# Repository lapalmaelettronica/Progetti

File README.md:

# Progetti
Una lista dei progetti che ho pubblicato su instagram, potete trovarci pcb, codici, schemi elettrici e stampe 3d!

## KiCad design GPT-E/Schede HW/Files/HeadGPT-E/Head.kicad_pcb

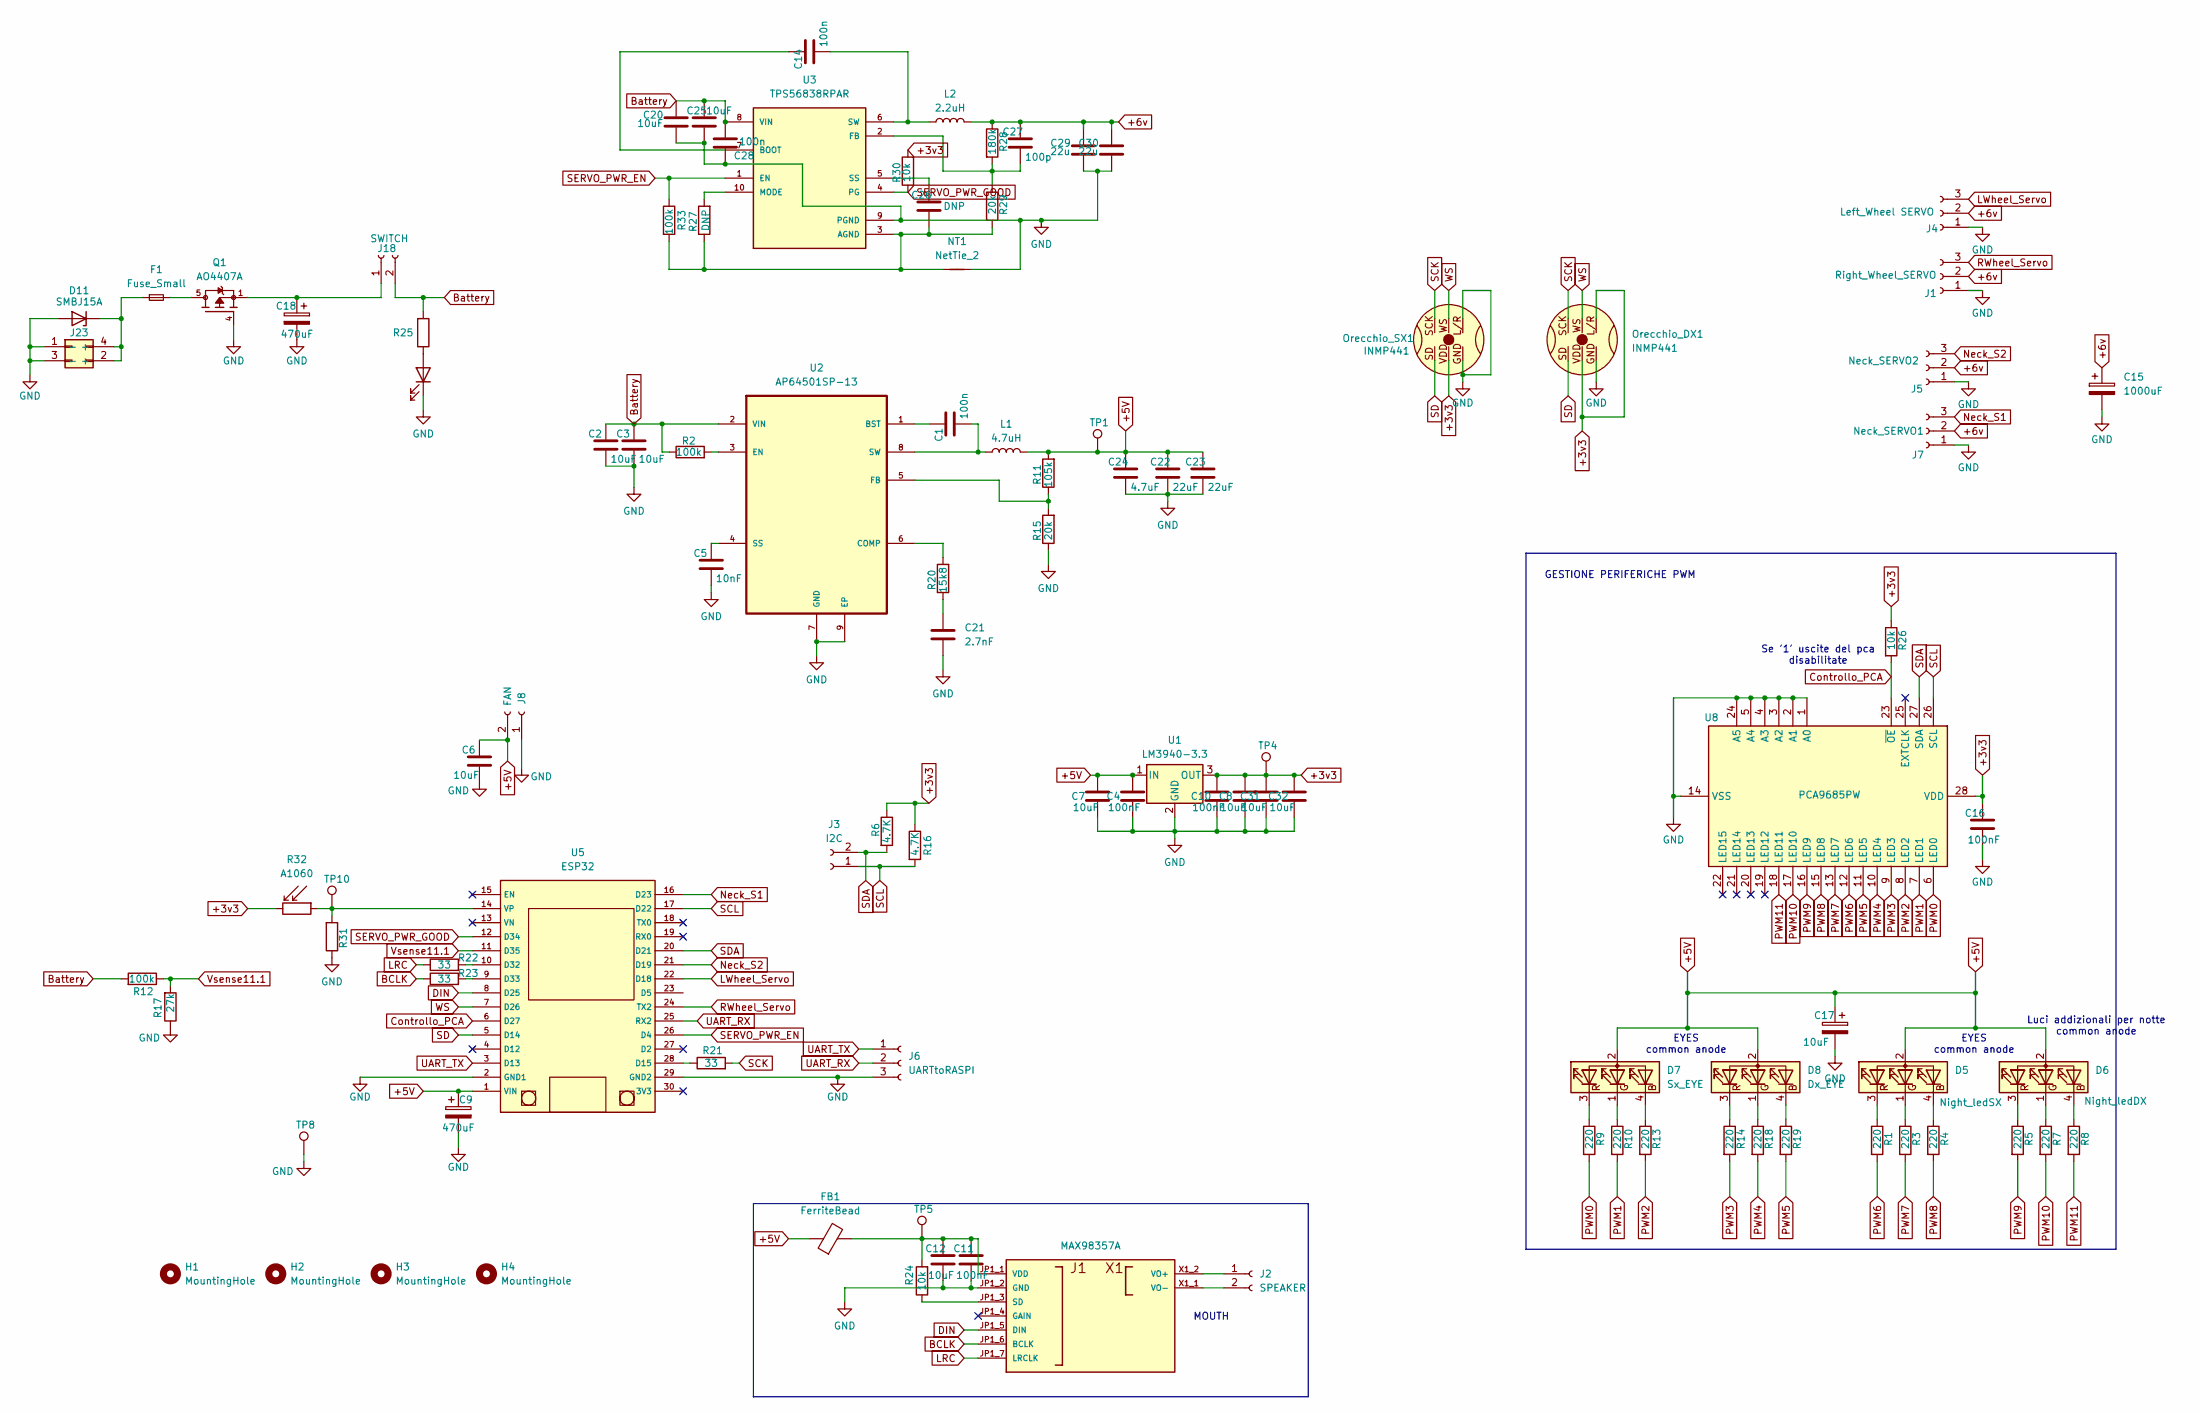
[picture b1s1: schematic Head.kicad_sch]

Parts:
C1, C14, C28: 100n; C_0805_2012Metric_Pad1.18x1.45mm_HandSolder
C2, C3, C6, C7, C8, C12, C20, C25, C31, C32: 10uF; C_0805_2012Metric_Pad1.18x1.45mm_HandSolder
C4, C10, C11, C16: 100nF; C_0805_2012Metric_Pad1.18x1.45mm_HandSolder
C5: 10nF; C_0805_2012Metric_Pad1.18x1.45mm_HandSolder
C9, C18: 470uF; CP_Radial_D5.0mm_P2.00mm
C15: 1000uF; CP_Radial_D12.5mm_P5.00mm
C17: 10uF; CP_Radial_D5.0mm_P2.00mm
C21: 2.7nF; C_Disc_D5.0mm_W2.5mm_P2.50mm
C22, C23: 22uF; C_0805_2012Metric_Pad1.18x1.45mm_HandSolder
C24: 4.7uF; C_0805_2012Metric_Pad1.18x1.45mm_HandSolder
C26: DNP; C_0805_2012Metric_Pad1.18x1.45mm_HandSolder
C27: 100p; C_0805_2012Metric_Pad1.18x1.45mm_HandSolder
C29, C30: 22u; C_0805_2012Metric_Pad1.18x1.45mm_HandSolder
D5: Night_ledSX; NS-Tech_Grove_1x04_P2mm_Vertical
D6: Night_ledDX; NS-Tech_Grove_1x04_P2mm_Vertical
D7: Sx_EYE; NS-Tech_Grove_1x04_P2mm_Vertical
D8: Dx_EYE; NS-Tech_Grove_1x04_P2mm_Vertical
D11: SMBJ15A; D_SMB_Handsoldering
D13: LED; LED_D4.0mm
F1: Fuse_Small; Fuseholder_Littelfuse_Nano2_154x
FB1: FerriteBead; L_0805_2012Metric_Pad1.05x1.20mm_HandSolder
H1, H2, H3, H4: MountingHole; MountingHole_3.2mm_M3_DIN965
J1: Right_Wheel_SERVO; Molex_KK-254_AE-6410-03A_1x03_P2.54mm_Vertical
J2: SPEAKER; Molex_KK-254_AE-6410-02A_1x02_P2.54mm_Vertical
J3: I2C; Molex_KK-254_AE-6410-02A_1x02_P2.54mm_Vertical
J4: Left_Wheel SERVO; Molex_KK-254_AE-6410-03A_1x03_P2.54mm_Vertical
J5: Neck_SERVO2; Molex_KK-254_AE-6410-03A_1x03_P2.54mm_Vertical
J6: UARTtoRASPI; Molex_KK-254_AE-6410-03A_1x03_P2.54mm_Vertical
J7: Neck_SERVO1; Molex_KK-254_AE-6410-03A_1x03_P2.54mm_Vertical
J8: FAN; Molex_KK-254_AE-6410-02A_1x02_P2.54mm_Vertical
J18: SWITCH; PinHeader_1x02_P2.54mm_Vertical
J23: Molex_Micro-Fit_3.0_43045-0400_2x02_P3.00mm_Horizontal
L1: 4.7uH; L_Changjiang_FXL0630
L2: 2.2uH; L_Changjiang_FXL0630
NT1: NetTie_2; NetTie-2_SMD_Pad0.5mm
Orecchio_DX1: INMP441
Orecchio_SX1: INMP441
Q1: AO4407A; SOIC127P600X175-8N; PARTREV I
R1, R3, R4, R5, R7, R8, R9, R10, R13, R14, R18, R19: 220; R_1206_3216Metric_Pad1.30x1.75mm_HandSolder
R2, R12, R33: 100k; R_1206_3216Metric_Pad1.30x1.75mm_HandSolder
R6, R16: 4.7K; R_1206_3216Metric_Pad1.30x1.75mm_HandSolder
R11: 105k; R_1206_3216Metric_Pad1.30x1.75mm_HandSolder
R15, R29: 20k; R_1206_3216Metric_Pad1.30x1.75mm_HandSolder
R17: 27k; R_1206_3216Metric_Pad1.30x1.75mm_HandSolder
R20: 15k8; R_1206_3216Metric_Pad1.30x1.75mm_HandSolder
R21, R22, R23: 33; R_1206_3216Metric_Pad1.30x1.75mm_HandSolder
R24, R26, R30, R31: 10k; R_1206_3216Metric_Pad1.30x1.75mm_HandSolder
R25: 470; R_1206_3216Metric_Pad1.30x1.75mm_HandSolder
R27: DNP; R_1206_3216Metric_Pad1.30x1.75mm_HandSolder
R28: 180k; R_1206_3216Metric_Pad1.30x1.75mm_HandSolder
R32: A1060; R_LDR_D6.4mm_P3.4mm_Vertical
TP1, TP4, TP5, TP8, TP10: TestPoint; TestPoint_Pad_D1.5mm
U1: LM3940-3.3; SOT-223-3_TabPin2
U2: AP64501SP-13
U3: TPS56838RPAR; CONV_TPS56838RPAR; PARTREV A
U5: ESP32
U7: MAX98357A; PARTREV A
U8: PCA9685PW; TSSOP-28_4.4x9.7mm_P0.65mm

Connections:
+3v3: C8.1, C10.1, C16.1, C31.1, C32.1, Orecchio_DX1.L/R, Orecchio_DX1.VDD, Orecchio_SX1.VDD, R6.1, R16.1, R26.1, R30.2, R32.2, TP4.1, U1.3 (OUT), U8.28 (VDD)
+5V: C4.1, C6.1, C7.1, C9.1, C17.1, C22.1, C23.1, C24.1, D5.2 (A), D6.2 (A), D7.2 (A), D8.2 (A), FB1.1, J8.2, L1.2, R11.2, TP1.1, U1.1 (IN), U5.1 (VIN)
+6v: C15.1, C27.1, C29.1, C30.1, J1.2, J4.2, J5.2, J7.2, L2.2, R28.1
BCLK: R23.1, U7.JP1_6 (BCLK)
Battery: C2.1, C3.1, C20.1, C25.1, C28.2, J18.2, R2.1, R12.2, R25.2, U2.2 (VIN), U3.8 (VIN)
Controllo_PCA: R26.2, U5.6 (D27), U8.23 (~OE)
DIN: U5.8 (D25), U7.JP1_5 (DIN)
GND: C2.2, C3.2, C4.2, C5.2, C6.2, C7.2, C8.2, C9.2, C10.2, C11.2, C12.2, C15.2, C16.2, C17.2, C18.2, C20.2, C21.2, C22.2, C23.2, C24.2, C25.2, C28.1, C29.2, C30.2, C31.2, C32.2, D11.2 (A), D13.1 (K), J1.1, J4.1, J5.1, J6.3, J7.1, J8.1, J23.1 (-), J23.3 (-), NT1.1, Orecchio_DX1.GND, Orecchio_SX1.GND, Orecchio_SX1.L/R, Q1.4, R15.1, R17.1, R31.1, TP8.1, U1.2 (GND), U2.7 (GND), U2.9 (EP), U3.9 (PGND), U5.2 (GND1), U5.29 (GND2), U7.JP1_2 (GND), U8.1 (A0), U8.2 (A1), U8.3 (A2), U8.4 (A3), U8.5 (A4), U8.14 (VSS), U8.24 (A5)
LRC: R22.1, U7.JP1_7 (LRCLK)
LWheel_Servo: J4.3, U5.22 (D18)
Neck_S1: J7.3, U5.16 (D23)
Neck_S2: J5.3, U5.21 (D19)
unnamed: C21.1, R20.1
unnamed: D5.4 (BK), R4.1
unnamed: D5.1 (GK), R3.1
unnamed: D5.3 (RK), R1.1
unnamed: D6.4 (BK), R8.1
unnamed: D6.1 (GK), R7.1
unnamed: D6.3 (RK), R5.1
unnamed: D7.4 (BK), R13.1
unnamed: D7.1 (GK), R10.1
unnamed: D7.3 (RK), R9.1
unnamed: D8.4 (BK), R19.1
unnamed: D8.1 (GK), R18.1
unnamed: D8.3 (RK), R14.1
unnamed: D11.1 (K), F1.1, J23.2 (+), J23.4 (+)
unnamed: D13.2 (A), R25.1
unnamed: F1.2, Q1.5, Q1.6, Q1.7, Q1.8
unnamed: J2.1, U7.X1_2 (VO+)
unnamed: J2.2, U7.X1_1 (VO-)
unnamed: C18.1, J18.1, Q1.1, Q1.2, Q1.3
unnamed: C1.1, U2.1 (BST)
unnamed: R20.2, U2.6 (COMP)
unnamed: R2.2, U2.3 (EN)
unnamed: R11.1, R15.2, U2.5 (FB)
unnamed: C5.1, U2.4 (SS)
unnamed: C1.2, L1.1, U2.8 (SW)
unnamed: C26.2, NT1.2, R27.1, R29.2, R33.2, U3.3 (AGND)
unnamed: C14.1, U3.7 (BOOT)
unnamed: C27.2, R28.2, R29.1, U3.2 (FB)
unnamed: R27.2, U3.10 (MODE)
unnamed: C26.1, U3.5 (SS)
unnamed: C14.2, L2.1, U3.6 (SW)
unnamed: R21.1, U5.28 (D15)
unnamed: R22.2, U5.10 (D32)
unnamed: R23.2, U5.9 (D33)
unnamed: R31.2, R32.1, TP10.1, U5.14 (VP)
unnamed: R24.1, U7.JP1_3 (SD)
unnamed: C11.1, C12.1, FB1.2, R24.2, TP5.1, U7.JP1_1 (VDD)
PWM0: R9.2, U8.6 (LED0)
PWM1: R10.2, U8.7 (LED1)
PWM2: R13.2, U8.8 (LED2)
PWM3: R14.2, U8.9 (LED3)
PWM4: R18.2, U8.10 (LED4)
PWM5: R19.2, U8.11 (LED5)
PWM6: R1.2, U8.12 (LED6)
PWM7: R3.2, U8.13 (LED7)
PWM8: R4.2, U8.15 (LED8)
PWM9: R5.2, U8.16 (LED9)
PWM10: R7.2, U8.17 (LED10)
PWM11: R8.2, U8.18 (LED11)
RWheel_Servo: J1.3, U5.24 (TX2)
SCK: Orecchio_DX1.SCK, Orecchio_SX1.SCK, R21.2
SCL: J3.1, R16.2, U5.17 (D22), U8.26 (SCL)
SD: Orecchio_DX1.SD, Orecchio_SX1.SD, U5.5 (D14)
SDA: J3.2, R6.2, U5.20 (D21), U8.27 (SDA)
SERVO_PWR_EN: R33.1, U3.1 (EN), U5.26 (D4)
SERVO_PWR_GOOD: R30.1, U3.4 (PG), U5.12 (D34)
UART_RX: J6.2, U5.25 (RX2)
UART_TX: J6.1, U5.3 (D13)
Vsense11.1: R12.1, R17.2, U5.11 (D35)
WS: Orecchio_DX1.WS, Orecchio_SX1.WS, U5.7 (D26)

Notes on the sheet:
MOUTH
GESTIONE PERIFERICHE PWM
Se '1' uscite del pca disabilitate
EYES common anode
Luci addizionali per notte common anode

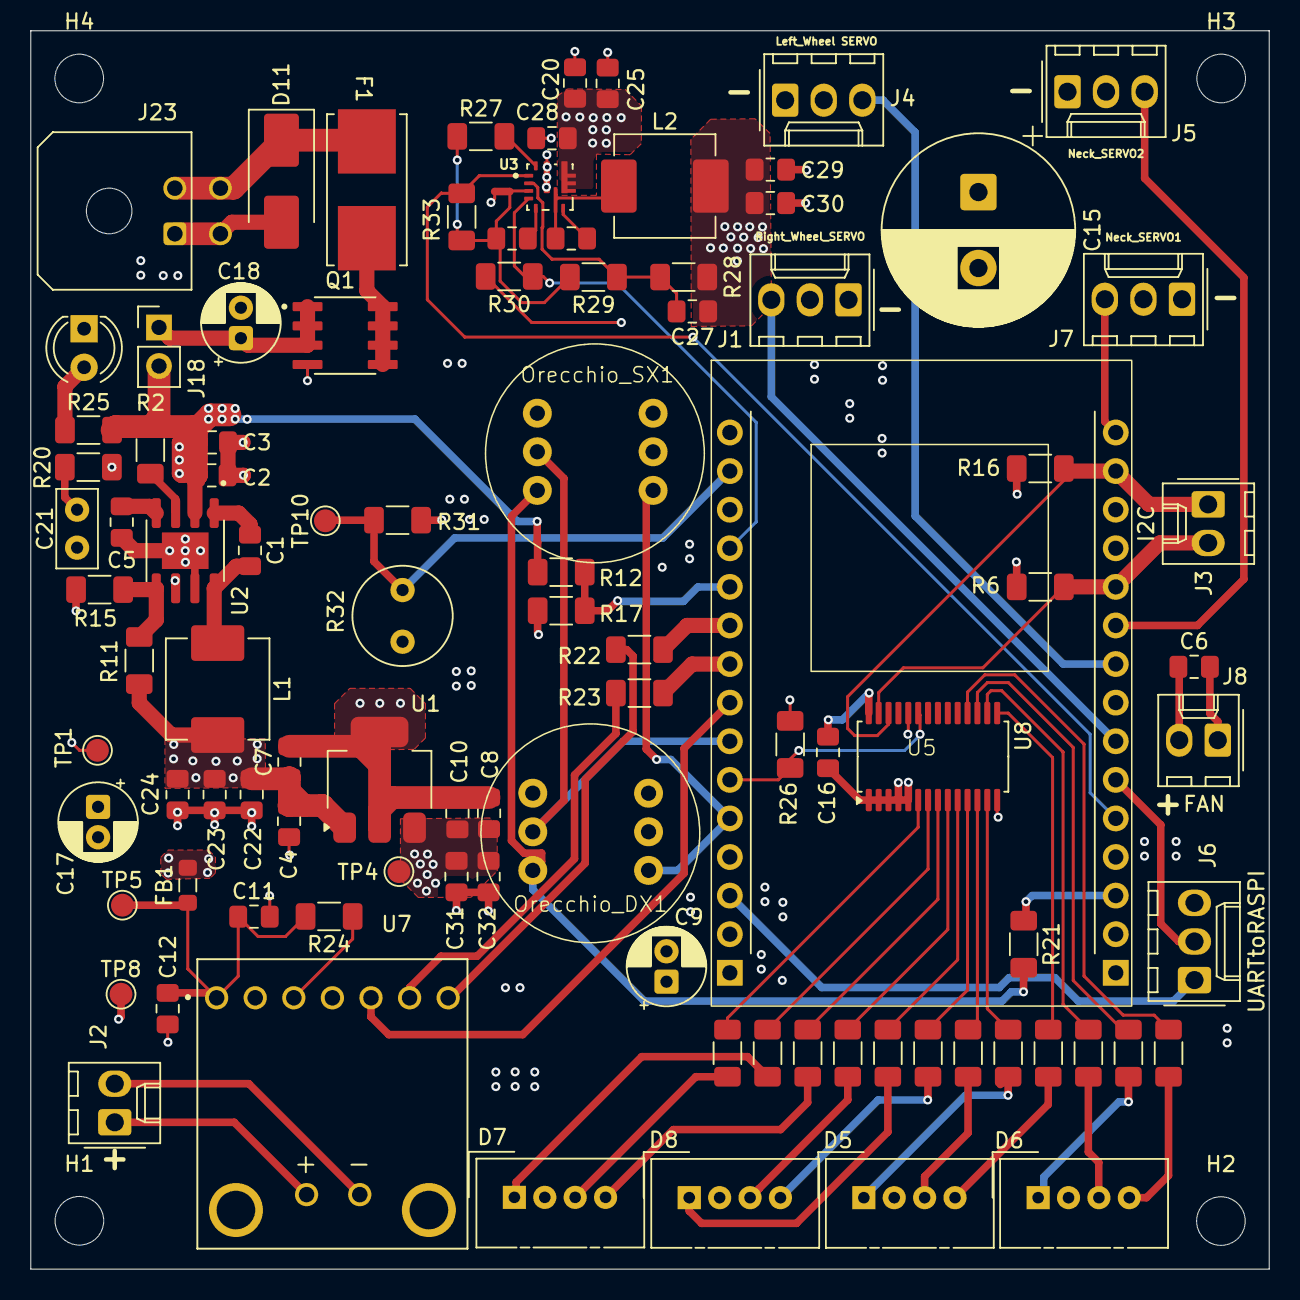
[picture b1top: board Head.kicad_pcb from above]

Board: 4 copper layers, 81.5 x 81.5 mm, 102 parts (0 on the bottom side), 72 nets.

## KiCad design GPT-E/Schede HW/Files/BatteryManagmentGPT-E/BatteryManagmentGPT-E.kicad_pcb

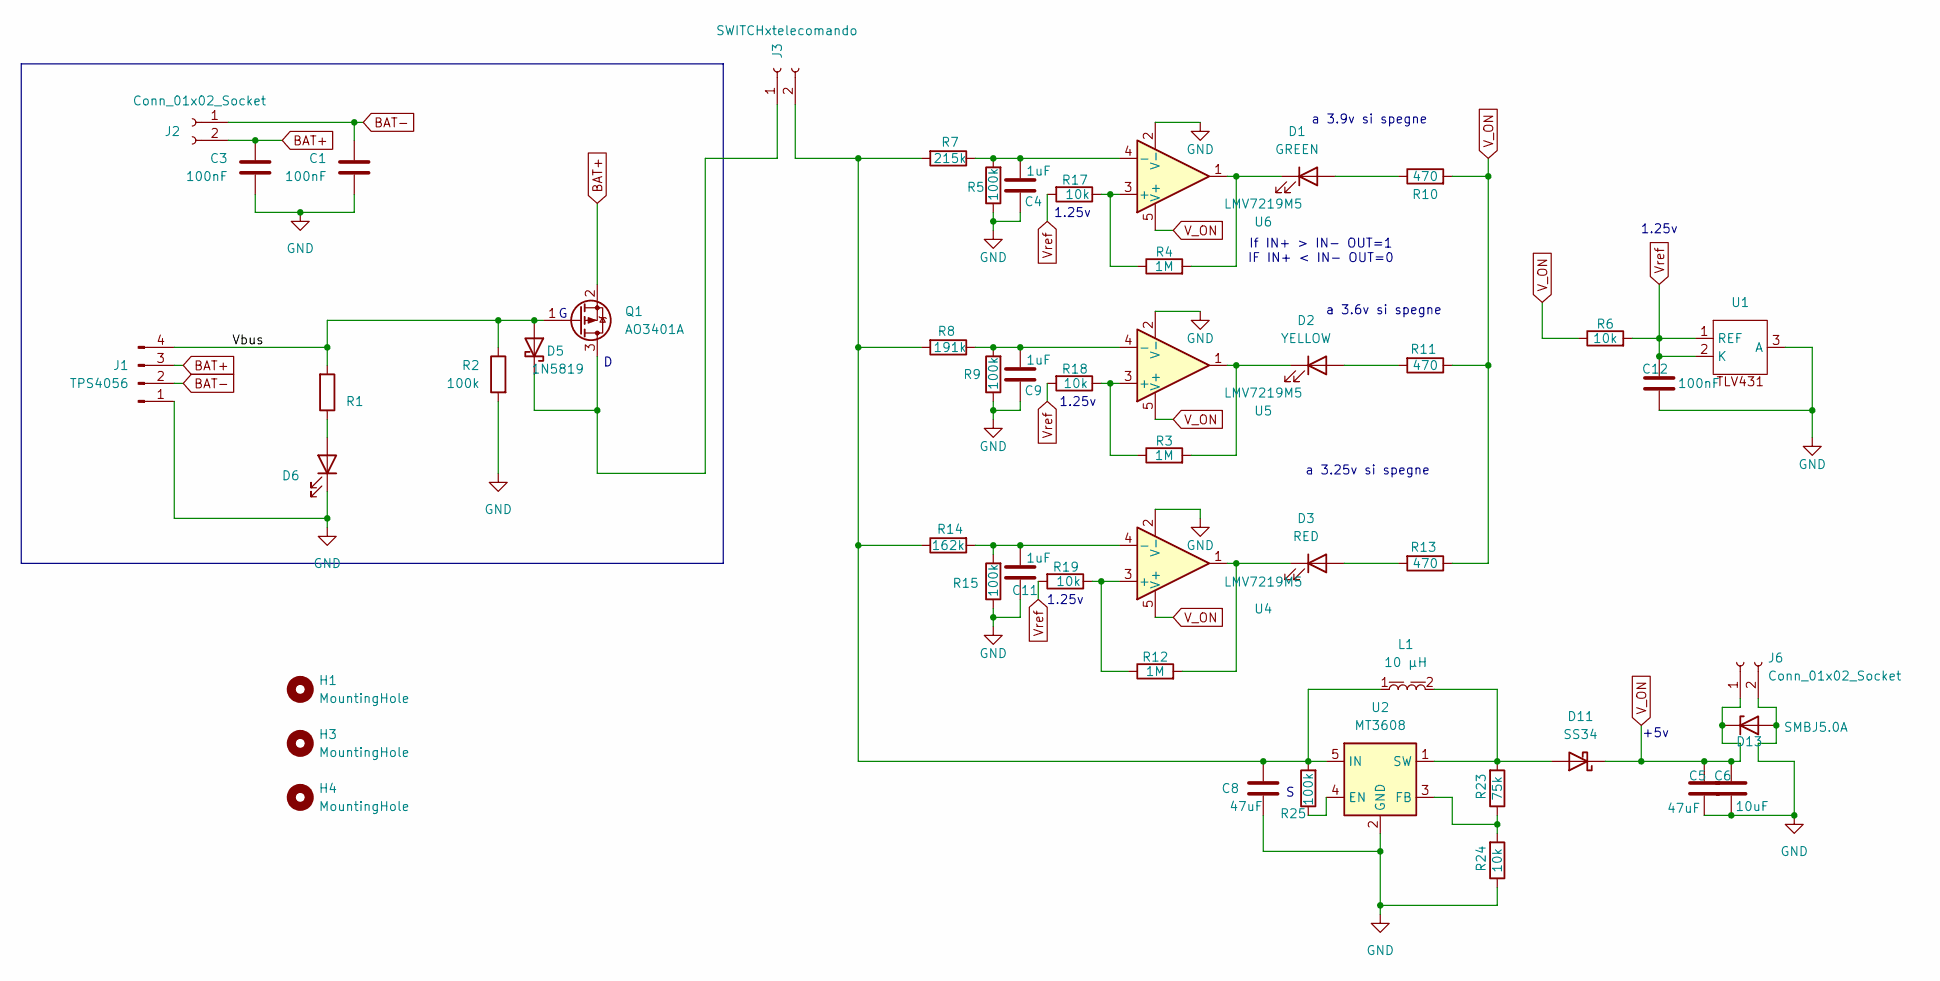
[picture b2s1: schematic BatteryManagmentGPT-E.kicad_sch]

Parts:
C1, C3, C12: 100nF; C_0805_2012Metric
C4, C9, C11: 1uF; C_0805_2012Metric
C5, C8: 47uF; C_0805_2012Metric
C6: 10uF; C_0805_2012Metric
D1: GREEN; LED_D4.0mm
D2: YELLOW; LED_D4.0mm
D3: RED; LED_D4.0mm
D5: 1N5819; D_DO-41_SOD81_P7.62mm_Horizontal
D6: LED; LED_D4.0mm
D11: SS34; D_SMB_Handsoldering
D13: SMBJ5.0A; D_SMB_Handsoldering
H1, H3, H4: MountingHole; MountingHole_2.2mm_M2
J1: TPS4056; Molex_KK-254_AE-6410-04A_1x04_P2.54mm_Vertical
J2, J6: Conn_01x02_Socket; TE_440054-2_1x02_P2.00mm_Vertical
J3: SWITCHxtelecomando; PinHeader_1x02_P2.54mm_Vertical
L1: Induttore 4020_7843845030100; L_Coilcraft_XxL4020; Part Number 78438440200016
Q1: AO3401A; SOT-23
R1, R10, R11, R13: 470; R_1206_3216Metric
R2, R5, R9, R15, R25: 100k; R_1206_3216Metric
R3, R4, R12: 1M; R_1206_3216Metric
R6, R17, R18, R19, R24: 10k; R_1206_3216Metric
R7: 215k; R_1206_3216Metric
R8: 191k; R_1206_3216Metric
R14: 162k; R_1206_3216Metric
R23: 75k; R_1206_3216Metric
U1: SOT-23-3
U2: MT3608; SOT-23-6_Handsoldering
U4, U5, U6: LMV7219M5; SOT-23-5_HandSoldering

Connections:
/Vbus: D5.2 (A), J1.4, Q1.1 (G), R1.2, R2.1
BAT+: C3.1, J1.3, J2.2, Q1.2 (S)
BAT-: C1.1, J1.2, J2.1
GND: C1.2, C3.2, C4.2, C5.2, C6.2, C8.2, C9.2, C11.2, C12.2, D6.1 (K), D13.2 (A), J1.1, J6.2, R2.2, R5.1, R9.1, R15.1, R24.1, U1.3 (A), U2.2 (GND), U4.2 (V-), U5.2 (V-), U6.2 (V-)
unnamed: D1.2 (A), R10.1
unnamed: D1.1 (K), R4.2, U6.1
unnamed: D2.2 (A), R11.2
unnamed: D2.1 (K), R3.2, U5.1
unnamed: D3.2 (A), R13.2
unnamed: D3.1 (K), R12.2, U4.1
unnamed: D5.1 (K), J3.1, Q1.3 (D)
unnamed: D6.2 (A), R1.1
unnamed: D11.2 (A), L1.2, R23.2, U2.1 (SW)
unnamed: C8.1, J3.2, L1.1, R7.2, R8.2, R14.1, R25.2, U2.5 (IN)
unnamed: R25.1, U2.4 (EN)
unnamed: R23.1, R24.2, U2.3 (FB)
unnamed: R12.1, R19.1, U4.3 (+)
unnamed: C11.1, R14.2, R15.2, U4.4 (-)
unnamed: R3.1, R18.1, U5.3 (+)
unnamed: C9.1, R8.1, R9.2, U5.4 (-)
unnamed: R4.1, R17.1, U6.3 (+)
unnamed: C4.1, R5.2, R7.1, U6.4 (-)
V_ON: C5.1, C6.1, D11.1 (K), D13.1 (K), J6.1, R6.1, R10.2, R11.1, R13.1, U4.5 (V+), U5.5 (V+), U6.5 (V+)
Vref: C12.1, R6.2, R17.2, R18.2, R19.2, U1.1 (REF), U1.2 (K)

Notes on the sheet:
If IN+ > IN- OUT=1 IF IN+ < IN- OUT=0
a 3.9v si spegne
1.25v
a 3.6v si spegne
a 3.25v si spegne
+5v

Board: 2 copper layers, 52 parts (0 on the bottom side), 24 nets, no tracks yet.

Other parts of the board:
H1#2: MountingHole; MountingHole_2.2mm_M2

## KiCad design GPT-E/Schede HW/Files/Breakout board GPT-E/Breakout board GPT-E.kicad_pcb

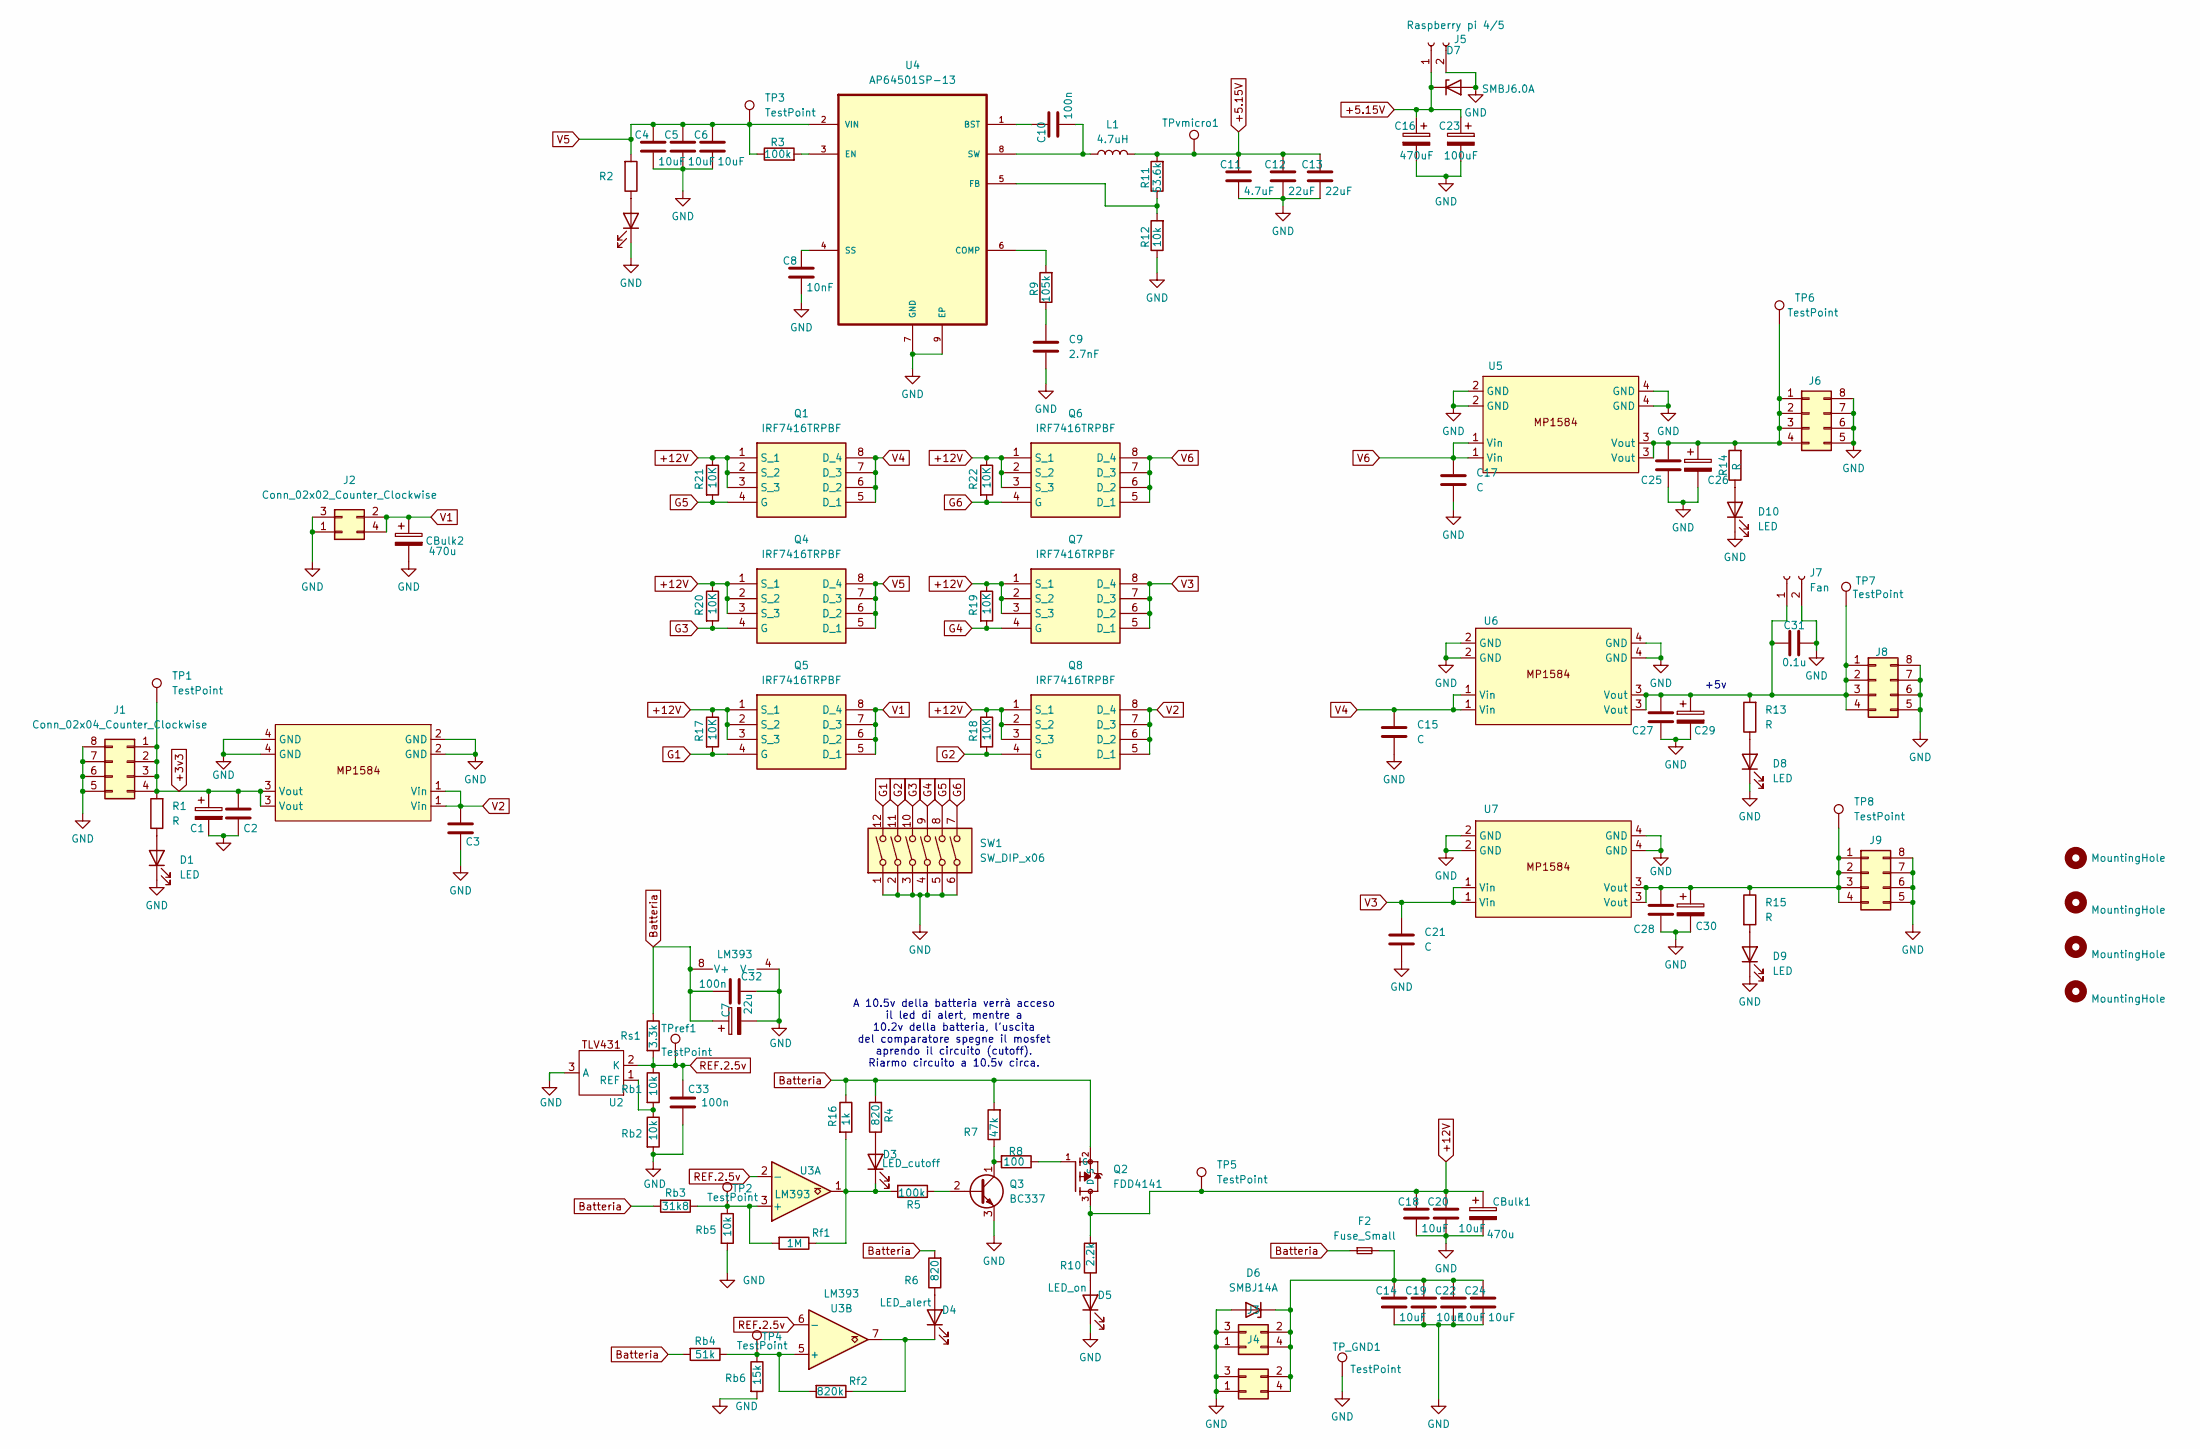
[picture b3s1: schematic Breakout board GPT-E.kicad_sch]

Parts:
C1, C26, C29, C30: C_Polarized; CP_Radial_D6.3mm_P2.50mm
C2, C3, C15, C17, C21, C25, C27, C28: C; C_Disc_D5.1mm_W3.2mm_P5.00mm
C4, C5, C6, C14, C18, C19, C20, C22, C24: 10uF; C_0805_2012Metric_Pad1.18x1.45mm_HandSolder
C7: 22u; CP_Radial_D4.0mm_P1.50mm
C8: 10nF; C_0805_2012Metric_Pad1.18x1.45mm_HandSolder
C9: 2.7nF; C_Disc_D5.0mm_W2.5mm_P2.50mm
C10, C32, C33: 100n; C_0805_2012Metric_Pad1.18x1.45mm_HandSolder
C11: 4.7uF; C_0805_2012Metric_Pad1.18x1.45mm_HandSolder
C12, C13: 22uF; C_0805_2012Metric_Pad1.18x1.45mm_HandSolder
C16: 470uF; CP_Radial_D5.0mm_P2.00mm
C23: 100uF; CP_Radial_D5.0mm_P2.00mm
C31: 0.1u; C_Disc_D5.1mm_W3.2mm_P5.00mm
CBulk1, CBulk2: 470u; CP_Radial_D6.3mm_P2.50mm
D1, D2, D8, D9, D10: LED; LED_D4.0mm
D3: LED_cutoff; LED_D4.0mm
D4: LED_alert; LED_D4.0mm
D5: LED_on; LED_D4.0mm
D6: SMBJ14A; D_SMB_Handsoldering
D7: SMBJ6.0A; D_SMB_Handsoldering
F2: Fuse_Small; Fuseholder_Littelfuse_Nano2_154x
H1, H2, H3, H4: MountingHole; MountingHole_3.2mm_M3
J1, J6, J8, J9: Conn_02x04_Counter_Clockwise; Molex_Micro-Fit_3.0_43045-0812_2x04_P3.00mm_Vertical
J2, J4: Conn_02x02_Counter_Clockwise; Molex_Micro-Fit_3.0_43045-0412_2x02_P3.00mm_Vertical
J3: Conn_02x02_Counter_Clockwise; Molex_Micro-Fit_3.0_43045-0400_2x02_P3.00mm_Horizontal
J5: Raspberry pi 4/5; TerminalBlock_TE_282834-2_1x02_P2.54mm_Horizontal
J7: Fan; PinHeader_1x02_P2.54mm_Vertical
L1: 4.7uH; L_Changjiang_FXL0630
Q1, Q4, Q5, Q6, Q7, Q8: IRF7416TRPBF; SOIC-8; Mouser Part Number 942-IRF7416TRPBF
Q2: FDD4141; FDD4141-TO252
Q3: BC337; TO-92L_HandSolder
R1, R13, R14, R15: R; R_Axial_DIN0204_L3.6mm_D1.6mm_P5.08mm_Horizontal
R2: 470; R_1206_3216Metric_Pad1.30x1.75mm_HandSolder
R3, R5: 100k; R_1206_3216Metric_Pad1.30x1.75mm_HandSolder
R4, R6: 820; R_1206_3216Metric_Pad1.30x1.75mm_HandSolder
R7: 47k; R_1206_3216Metric_Pad1.30x1.75mm_HandSolder
R8: 100; R_1206_3216Metric_Pad1.30x1.75mm_HandSolder
R9: 105k; R_1206_3216Metric_Pad1.30x1.75mm_HandSolder
R10: 2.2k; R_Axial_DIN0204_L3.6mm_D1.6mm_P5.08mm_Horizontal
R11: 53.6k; R_1206_3216Metric_Pad1.30x1.75mm_HandSolder
R12: 10k; R_1206_3216Metric_Pad1.30x1.75mm_HandSolder
R16: 1k; R_1206_3216Metric_Pad1.30x1.75mm_HandSolder
R17, R18, R19, R20, R21, R22: 10K; R_1206_3216Metric_Pad1.30x1.75mm_HandSolder
Rb1, Rb2, Rb5: 10k; R_1206_3216Metric_Pad1.30x1.75mm_HandSolder
Rb3: 31k8; R_1206_3216Metric_Pad1.30x1.75mm_HandSolder
Rb4: 51k; R_1206_3216Metric_Pad1.30x1.75mm_HandSolder
Rb6: 15k; R_1206_3216Metric_Pad1.30x1.75mm_HandSolder
Rf1: 1M; R_1206_3216Metric_Pad1.30x1.75mm_HandSolder
Rf2: 820k; R_1206_3216Metric_Pad1.30x1.75mm_HandSolder
Rs1: 3.3k; R_1206_3216Metric_Pad1.30x1.75mm_HandSolder
SW1: SW_DIP_x06; SW_DIP_SPSTx06_Slide_6.7x16.8mm_W7.62mm_P2.54mm_LowProfile
TP1, TP2, TP3, TP4, TP5, TP6, TP7, TP8: TestPoint; TestPoint_Pad_D1.5mm
TP_GND1: TestPoint; TestPoint_Pad_D1.5mm
TPref1: TestPoint; TestPoint_Pad_D1.5mm
TPvmicro1: TestPoint; TestPoint_Pad_D1.5mm
U1, U5, U6, U7: MP1584EN
U2: SOT-23-3
U3: LM393; DIP-8_W7.62mm
U4: AP64501SP-13

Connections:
+3v3: C1.1, C2.1, J1.1, J1.2, J1.3, J1.4, R1.2, TP1.1, U1.3 (Vout)
+5.15V: C11.1, C12.1, C13.1, C16.1, C23.1, D7.1 (K), J5.1, L1.2, R11.2, TPvmicro1.1
+12V: C18.1, C20.1, CBulk1.1, Q1.1 (S_1), Q1.2 (S_2), Q1.3 (S_3), Q2.3 (D), Q4.1 (S_1), Q4.2 (S_2), Q4.3 (S_3), Q5.1 (S_1), Q5.2 (S_2), Q5.3 (S_3), Q6.1 (S_1), Q6.2 (S_2), Q6.3 (S_3), Q7.1 (S_1), Q7.2 (S_2), Q7.3 (S_3), Q8.1 (S_1), Q8.2 (S_2), Q8.3 (S_3), R10.2, R17.1, R18.1, R19.1, R20.1, R21.1, R22.1, TP5.1
Batteria: C7.1, C32.1, F2.1, Q2.2 (S), R4.2, R6.2, R7.2, R16.1, Rb3.2, Rb4.2, Rs1.1, U3.8 (V+)
G1: Q5.4 (G), R17.2, SW1.12
G2: Q8.4 (G), R18.2, SW1.11
G3: Q4.4 (G), R20.2, SW1.10
G4: Q7.4 (G), R19.2, SW1.9
G5: Q1.4 (G), R21.2, SW1.8
G6: Q6.4 (G), R22.2, SW1.7
GND: C1.2, C2.2, C3.2, C4.2, C5.2, C6.2, C7.2, C8.2, C9.2, C11.2, C12.2, C13.2, C14.2, C15.2, C16.2, C17.2, C18.2, C19.2, C20.2, C21.2, C22.2, C23.2, C24.2, C25.2, C26.2, C27.2, C28.2, C29.2, C30.2, C31.2, C32.2, C33.2, CBulk1.2, CBulk2.2, D1.1 (K), D2.1 (K), D5.1 (K), D6.2 (A), D7.2 (A), D8.1 (K), D9.1 (K), D10.1 (K), J1.5, J1.6, J1.7, J1.8, J2.1, J2.3, J3.1, J3.3, J4.1, J4.3, J5.2, J6.5, J6.6, J6.7, J6.8, J7.2, J8.5, J8.6, J8.7, J8.8, J9.5, J9.6, J9.7, J9.8, Q3.3 (E), R12.1, Rb2.2, Rb5.2, Rb6.2, SW1.1, SW1.2, SW1.3, SW1.4, SW1.5, SW1.6, TP_GND1.1, U1.2 (GND), U1.4 (GND), U2.3 (A), U3.4 (V-), U4.7 (GND), U4.9 (EP), U5.2 (GND), U5.4 (GND), U6.2 (GND), U6.4 (GND), U7.2 (GND), U7.4 (GND)
unnamed: C9.1, R9.1
unnamed: D1.2 (A), R1.1
unnamed: D2.2 (A), R2.1
unnamed: D3.2 (A), R4.1
unnamed: D3.1 (K), R5.2, R16.2, Rf1.1, U3.1
unnamed: D4.2 (A), R6.1
unnamed: D4.1 (K), Rf2.1, U3.7
unnamed: D5.2 (A), R10.1
unnamed: C14.1, C19.1, C22.1, C24.1, D6.1 (K), F2.2, J3.2, J3.4, J4.2, J4.4
unnamed: D8.2 (A), R13.1
unnamed: D9.2 (A), R15.2
unnamed: D10.2 (A), R14.1
unnamed: C25.1, C26.1, J6.1, J6.2, J6.3, J6.4, R14.2, TP6.1, U5.3 (Vout)
unnamed: C27.1, C29.1, C31.1, J7.1, J8.1, J8.2, J8.3, J8.4, R13.2, TP7.1, U6.3 (Vout)
unnamed: C28.1, C30.1, J9.1, J9.2, J9.3, J9.4, R15.1, TP8.1, U7.3 (Vout)
unnamed: Q2.1 (G), R8.1
unnamed: Q3.2 (B), R5.1
unnamed: Q3.1 (C), R7.1, R8.2
unnamed: Rb1.2, Rb2.1, U2.1 (REF)
unnamed: Rb3.1, Rb5.1, Rf1.2, TP2.1, U3.3 (+)
unnamed: Rb4.1, Rb6.1, Rf2.2, TP4.1, U3.5 (+)
unnamed: C10.1, U4.1 (BST)
unnamed: R9.2, U4.6 (COMP)
unnamed: R3.2, U4.3 (EN)
unnamed: R11.1, R12.2, U4.5 (FB)
unnamed: C8.1, U4.4 (SS)
unnamed: C10.2, L1.1, U4.8 (SW)
REF.2.5v: C33.1, Rb1.1, Rs1.2, TPref1.1, U2.2 (K), U3.2 (-), U3.6 (-)
V1: CBulk2.1, J2.2, J2.4, Q5.5 (D_1), Q5.6 (D_2), Q5.7 (D_3), Q5.8 (D_4)
V2: C3.1, Q8.5 (D_1), Q8.6 (D_2), Q8.7 (D_3), Q8.8 (D_4), U1.1 (Vin)
V3: C21.1, Q7.5 (D_1), Q7.6 (D_2), Q7.7 (D_3), Q7.8 (D_4), U7.1 (Vin)
V4: C15.1, Q1.5 (D_1), Q1.6 (D_2), Q1.7 (D_3), Q1.8 (D_4), U6.1 (Vin)
V5: C4.1, C5.1, C6.1, Q4.5 (D_1), Q4.6 (D_2), Q4.7 (D_3), Q4.8 (D_4), R2.2, R3.1, TP3.1, U4.2 (VIN)
V6: C17.1, Q6.5 (D_1), Q6.6 (D_2), Q6.7 (D_3), Q6.8 (D_4), U5.1 (Vin)

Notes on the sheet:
A 10.5v della batteria verrà acceso il led di alert, mentre a 10.2v della batteria, l'uscita del comparatore spegne il mosfet aprendo il circuito (cutoff). Riarmo circuito a 10.5v circa.
+5v

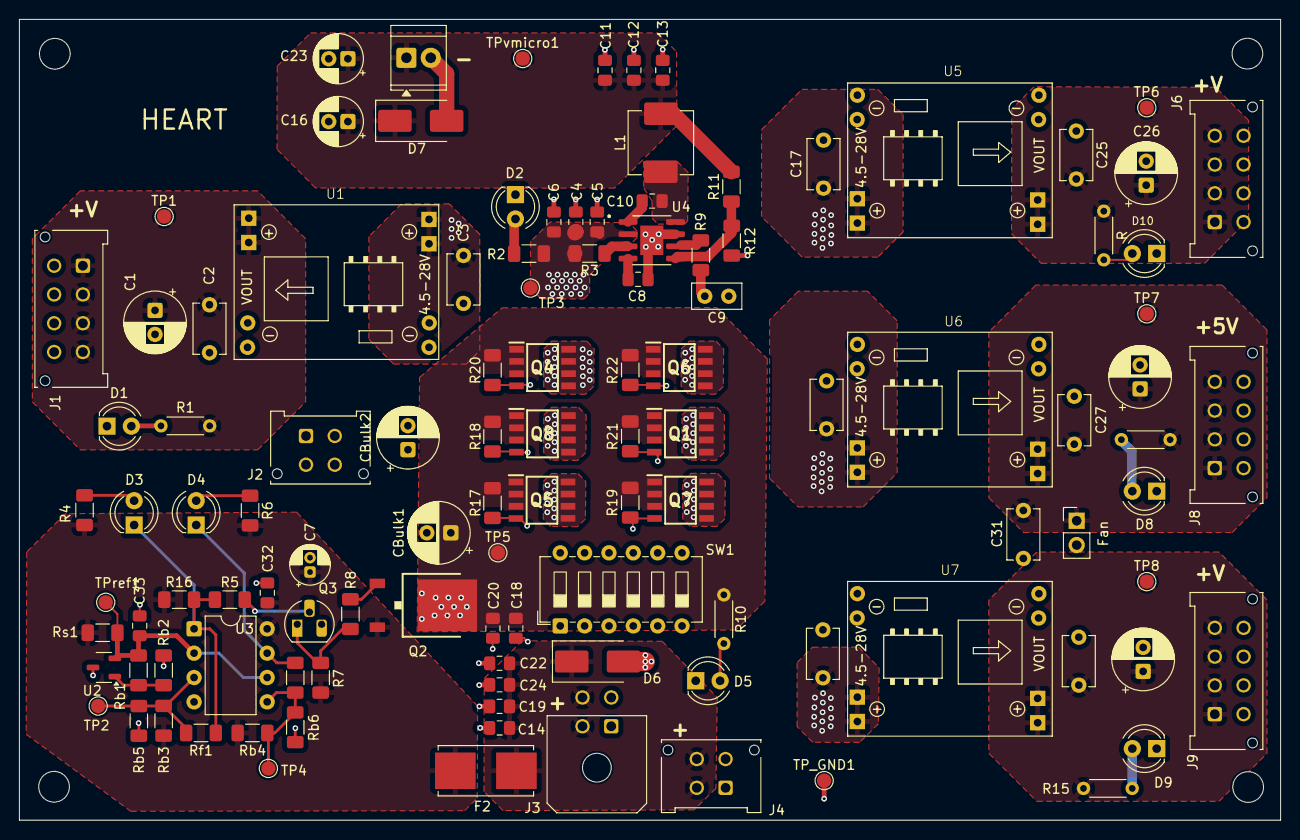
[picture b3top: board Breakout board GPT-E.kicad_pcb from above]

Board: 4 copper layers, 131.5 x 83.5 mm, 118 parts (0 on the bottom side), 45 nets.

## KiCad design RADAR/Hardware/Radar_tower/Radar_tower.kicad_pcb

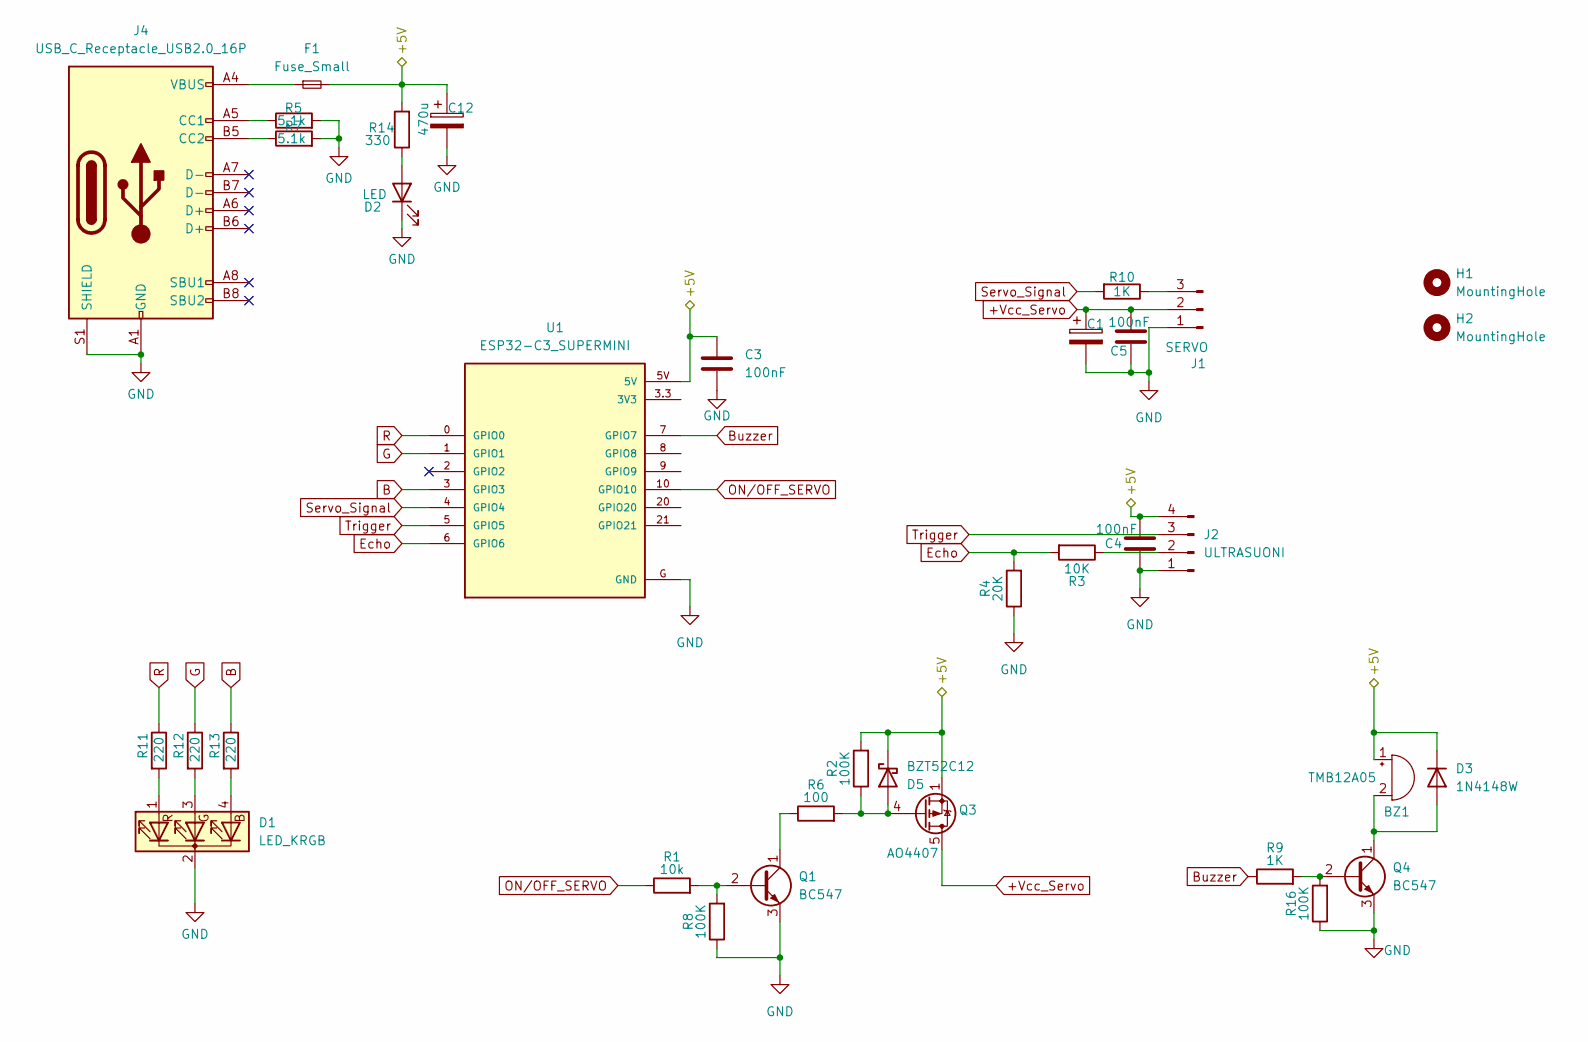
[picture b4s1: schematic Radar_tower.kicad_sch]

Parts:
BZ1: TMB12A05; Buzzer_12x9.5RM7.6
C1, C12: 470u; CP_Radial_D8.0mm_P3.50mm
C3, C4, C5: 100nF; C_0805_2012Metric_Pad1.18x1.45mm_HandSolder
D1: LED_KRGB; LED_D5.0mm-4_RGB_Wide_Pins
D2: LED; LED_D4.0mm
D3: 1N4148W; D_SOD-123
D5: BZT52C12; D_SOD-123
F1: Fuse_Small; Fuseholder_Littelfuse_Nano2_154x
H1, H2: MountingHole; MountingHole_2.2mm_M2
J1: SERVO; PinSocket_1x03_P2.54mm_Vertical
J2: ULTRASUONI; PinHeader_1x04_P2.54mm_Vertical
J4: USB_C_Receptacle_USB2.0_16P; USB_C_Receptacle_HRO_TYPE-C-31-M-12
Q1: BC547; TO-92L_HandSolder
Q3: AO4407; SOIC-8_3.9x4.9mm_P1.27mm
Q4: BC547; TO-92L_Inline
R1: 10k; R_1206_3216Metric_Pad1.30x1.75mm_HandSolder
R2, R8, R16: 100K; R_1206_3216Metric_Pad1.30x1.75mm_HandSolder
R3: 10K; R_1206_3216Metric_Pad1.30x1.75mm_HandSolder
R4: 20K; R_1206_3216Metric_Pad1.30x1.75mm_HandSolder
R5, R7: 5.1k; R_1206_3216Metric_Pad1.30x1.75mm_HandSolder
R6: 100; R_1206_3216Metric_Pad1.30x1.75mm_HandSolder
R9, R10: 1K; R_1206_3216Metric_Pad1.30x1.75mm_HandSolder
R11, R12, R13: 220; R_1206_3216Metric_Pad1.30x1.75mm_HandSolder
R14: 330; R_1206_3216Metric_Pad1.30x1.75mm_HandSolder
U1: ESP32-C3_SUPERMINI; MODULE_ESP32-C3_SUPERMINI

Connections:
+Vcc_Servo: C1.1, C5.1, J1.2, Q3.5 (D), Q3.6 (D), Q3.7 (D), Q3.8 (D)
/+5V: BZ1.1 (+), C3.1, C4.1, C12.1, D3.1 (K), D5.1 (K), F1.2, J2.4, Q3.1 (S), Q3.2 (S), Q3.3 (S), R2.2, R14.2, U1.5V
B: R13.1, U1.3 (GPIO3)
Buzzer: R9.1, U1.7 (GPIO7)
Echo: R3.2, R4.2, U1.6 (GPIO6)
G: R12.1, U1.1 (GPIO1)
GND: C1.2, C3.2, C4.2, C5.2, C12.2, D1.2 (K), D2.1 (K), J1.1, J2.1, J4.A1 (GND), J4.A12 (GND), J4.B1 (GND), J4.B12 (GND), J4.S1 (SHIELD), Q1.3 (E), Q4.3 (E), R4.1, R5.2, R7.2, R8.1, R16.1, U1.G (GND)
unnamed: BZ1.2 (-), D3.2 (A), Q4.1 (C)
unnamed: D1.4 (BA), R13.2
unnamed: D1.3 (GA), R12.2
unnamed: D1.1 (RA), R11.2
unnamed: D2.2 (A), R14.1
unnamed: D5.2 (A), Q3.4 (G), R2.1, R6.2
unnamed: F1.1, J4.A4 (VBUS), J4.A9 (VBUS), J4.B4 (VBUS), J4.B9 (VBUS)
unnamed: J1.3, R10.1
unnamed: J2.2, R3.1
unnamed: J4.A5 (CC1), R5.1
unnamed: J4.B5 (CC2), R7.1
unnamed: Q1.2 (B), R1.2, R8.2
unnamed: Q1.1 (C), R6.1
unnamed: Q4.2 (B), R9.2, R16.2
ON/OFF_SERVO: R1.1, U1.10 (GPIO10)
R: R11.1, U1.0 (GPIO0)
Servo_Signal: R10.2, U1.4 (GPIO4)
Trigger: J2.3, U1.5 (GPIO5)
